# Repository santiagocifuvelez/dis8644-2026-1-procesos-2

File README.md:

# dis8644-2026-1-procesos-2

Este repositorio estuvo activo entre marzo y abril 2026, durante la segunda mitad del curso DIS8644 Taller de diseño de máquinas electrónicas.

Para el contexto global del curso, por favor visitar el repositorio <https://github.com/disenoUDP/dis8644-2026-1>

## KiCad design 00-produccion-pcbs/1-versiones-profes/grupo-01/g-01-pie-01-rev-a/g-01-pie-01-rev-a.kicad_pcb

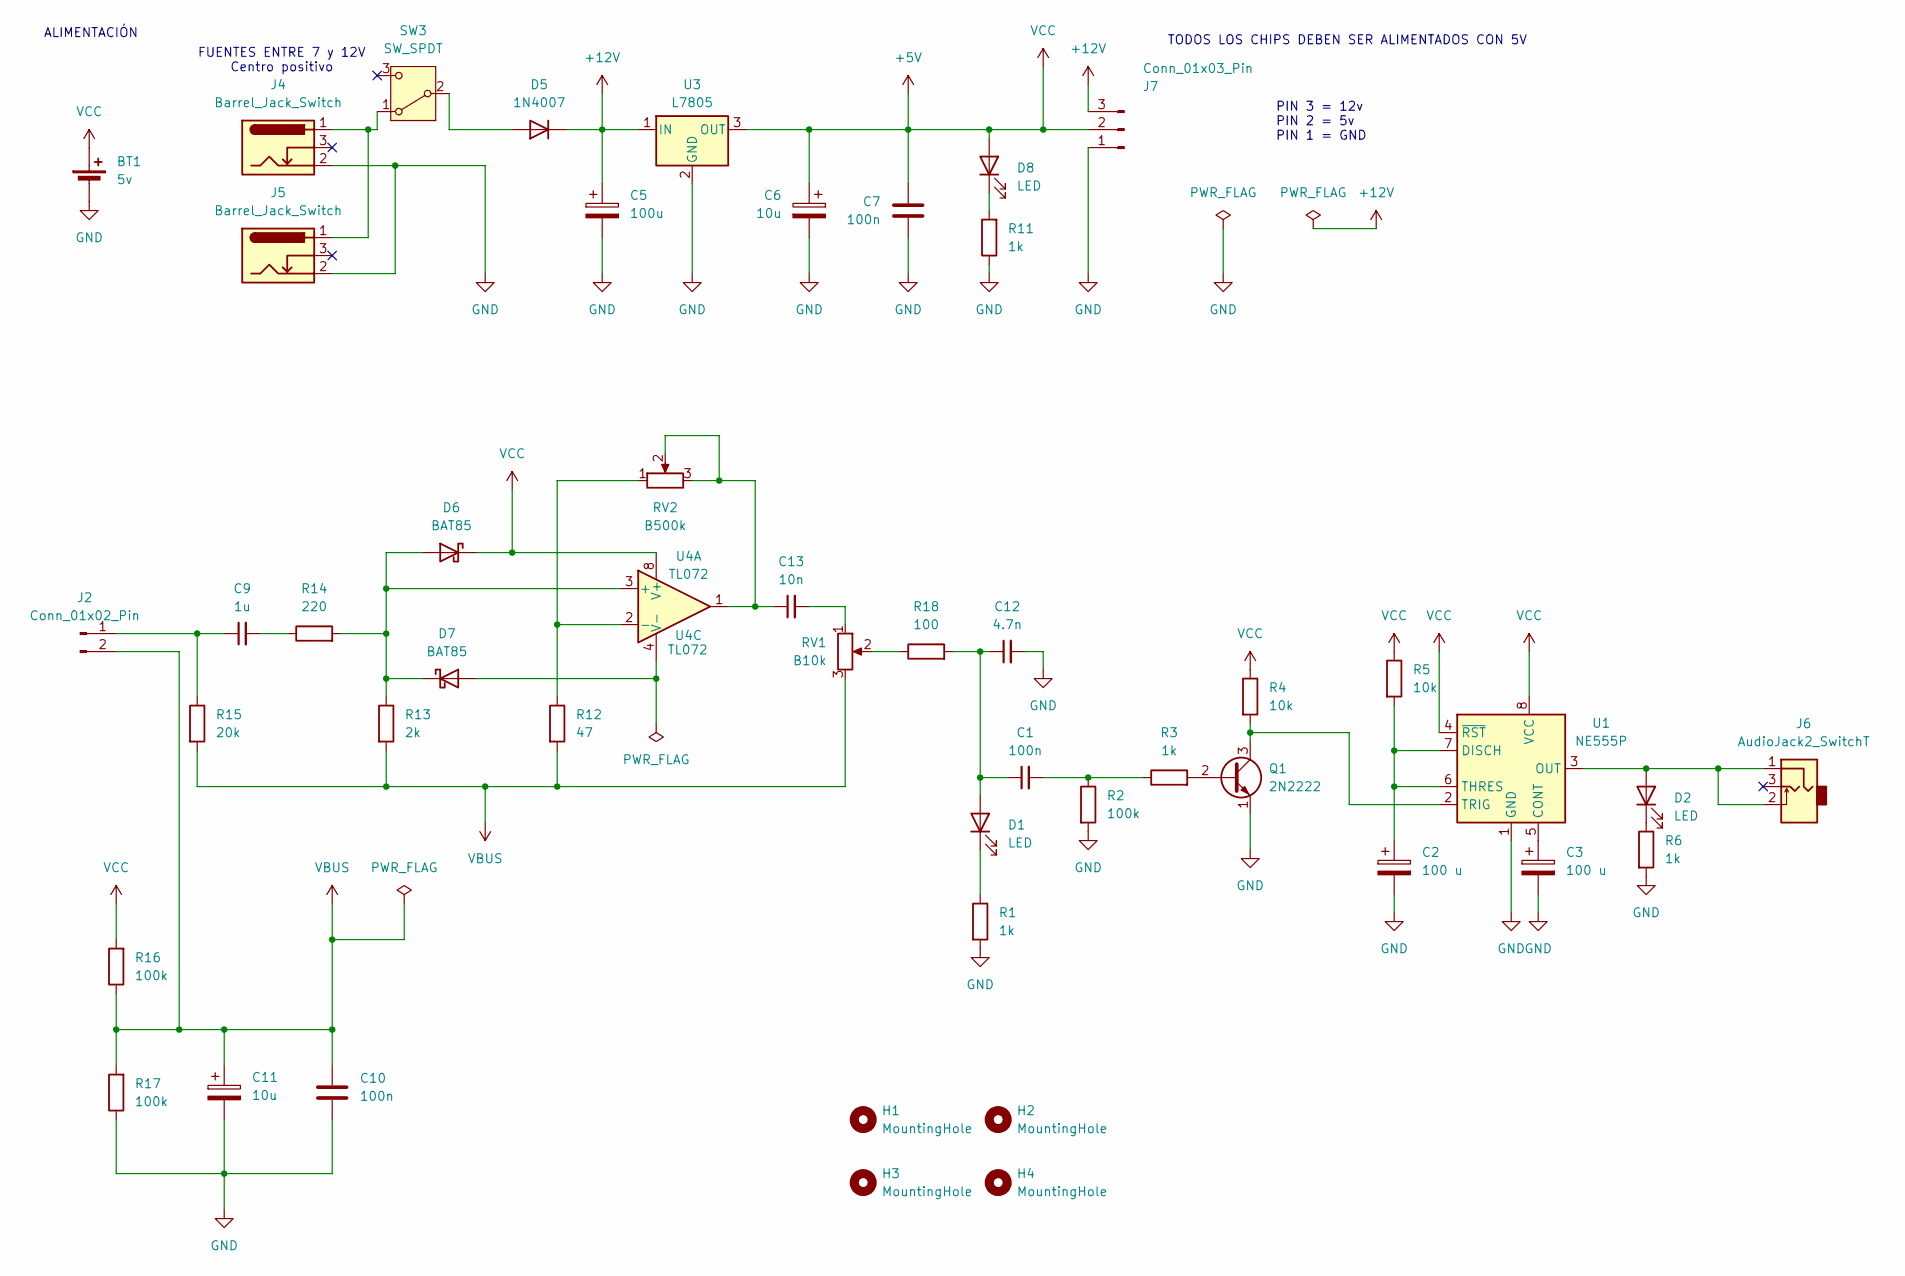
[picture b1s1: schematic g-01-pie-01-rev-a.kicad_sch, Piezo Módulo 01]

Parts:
BT1: 5v; TerminalBlock_MaiXu_MX126-5.0-02P_1x02_P5.00mm
C1, C7, C10: 100n; C_Disc_D5.0mm_W2.5mm_P2.50mm
C2, C3: 100 u; CP_Radial_D8.0mm_P3.80mm
C5: 100u; CP_Radial_D8.0mm_P3.80mm
C6, C11: 10u; CP_Radial_D4.0mm_P2.00mm
C9: 1u; C_Disc_D3.8mm_W2.6mm_P2.50mm
C12: 4.7n; C_Disc_D3.8mm_W2.6mm_P2.50mm
C13: 10n; C_Disc_D3.8mm_W2.6mm_P2.50mm
D1, D2, D8: LED; LED_D5.0mm
D5: 1N4007; D_DO-41_SOD81_P10.16mm_Horizontal
D6, D7: BAT85; D_DO-35_SOD27_P7.62mm_Horizontal
H1, H2, H3, H4: MountingHole; MountingHole_3.2mm_M3
J2: Conn_01x02_Pin; PinSocket_1x02_P2.54mm_Vertical
J4, J5: Barrel_Jack_Switch; BarrelJack_Horizontal
J6: AudioJack2_SwitchT; PJ301M-12
J7: Conn_01x03_Pin; PinSocket_1x03_P2.54mm_Vertical
Q1: 2N2222; TO-39-3
R1, R3, R6, R11: 1k; R_Axial_DIN0207_L6.3mm_D2.5mm_P10.16mm_Horizontal
R2, R16, R17: 100k; R_Axial_DIN0207_L6.3mm_D2.5mm_P10.16mm_Horizontal
R4, R5: 10k; R_Axial_DIN0207_L6.3mm_D2.5mm_P10.16mm_Horizontal
R12: 47; R_Axial_DIN0207_L6.3mm_D2.5mm_P10.16mm_Horizontal
R13: 2k; R_Axial_DIN0207_L6.3mm_D2.5mm_P10.16mm_Horizontal
R14: 220; R_Axial_DIN0207_L6.3mm_D2.5mm_P10.16mm_Horizontal
R15: 20k; R_Axial_DIN0207_L6.3mm_D2.5mm_P10.16mm_Horizontal
R18: 100; R_Axial_DIN0207_L6.3mm_D2.5mm_P10.16mm_Horizontal
RV1: B10k; Potentiometer_Alps_RK163_Single_Horizontal
RV2: B500k; Potentiometer_Alps_RK163_Single_Horizontal
SW3: SW_SPDT; spdt_ssd12d00g3
U1: NE555P; CERDIP-8_W7.62mm_SideBrazed_LongPads
U3: L7805; TO-220-3_Vertical
U4: TL072; CERDIP-8_W7.62mm_SideBrazed_LongPads

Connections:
+5V: BT1.1 (+), C6.1, C7.1, D6.1 (K), D8.2 (A), J7.2, R4.1, R5.1, R16.2, U1.4 (~RST), U1.8 (VCC), U3.3 (OUT), U4.8 (V+)
+12V: C5.1, D5.1 (K), J7.3, U3.1 (IN)
GND: BT1.2 (-), C2.2, C3.2, C5.2, C6.2, C7.2, C10.2, C11.2, C12.2, J4.2, J5.2, J7.1, Q1.1 (E), R1.2, R2.2, R6.2, R11.1, R17.1, U1.1 (GND), U3.2 (GND)
unnamed: C1.2, R2.1, R3.1
unnamed: C9.2, R14.1
unnamed: C13.1, RV2.2, RV2.3, U4.1
unnamed: C13.2, RV1.1
unnamed: C1.1, C12.1, D1.2 (A), R18.2
unnamed: D1.1 (K), R1.1
unnamed: D2.2 (A), J6.1, J6.2, U1.3 (OUT)
unnamed: D2.1 (K), R6.1
unnamed: D5.2 (A), SW3.2 (B)
unnamed: D6.2 (A), D7.1 (K), R13.1, R14.2, U4.3 (+)
unnamed: D7.2 (A), U4.4 (V-)
unnamed: D8.1 (K), R11.2
unnamed: C9.1, J2.1, R15.1
unnamed: Q1.2 (B), R3.2
unnamed: Q1.3 (C), R4.2, U1.2 (TRIG)
unnamed: R18.1, RV1.2
unnamed: J4.1, J5.1, SW3.1 (A)
unnamed: C3.1, U1.5 (CONT)
unnamed: C2.1, R5.2, U1.6 (THRES), U1.7 (DISCH)
unnamed: R12.1, RV2.1, U4.2 (-)
VBUS: C10.1, C11.1, J2.2, R12.2, R13.2, R15.2, R16.1, R17.2, RV1.3

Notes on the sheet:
TODOS LOS CHIPS DEBEN SER ALIMENTADOS CON 5V
PIN 3 = 12v PIN 2 = 5v PIN 1 = GND
FUENTES ENTRE 7 y 12V Centro positivo
ALIMENTACIÓN

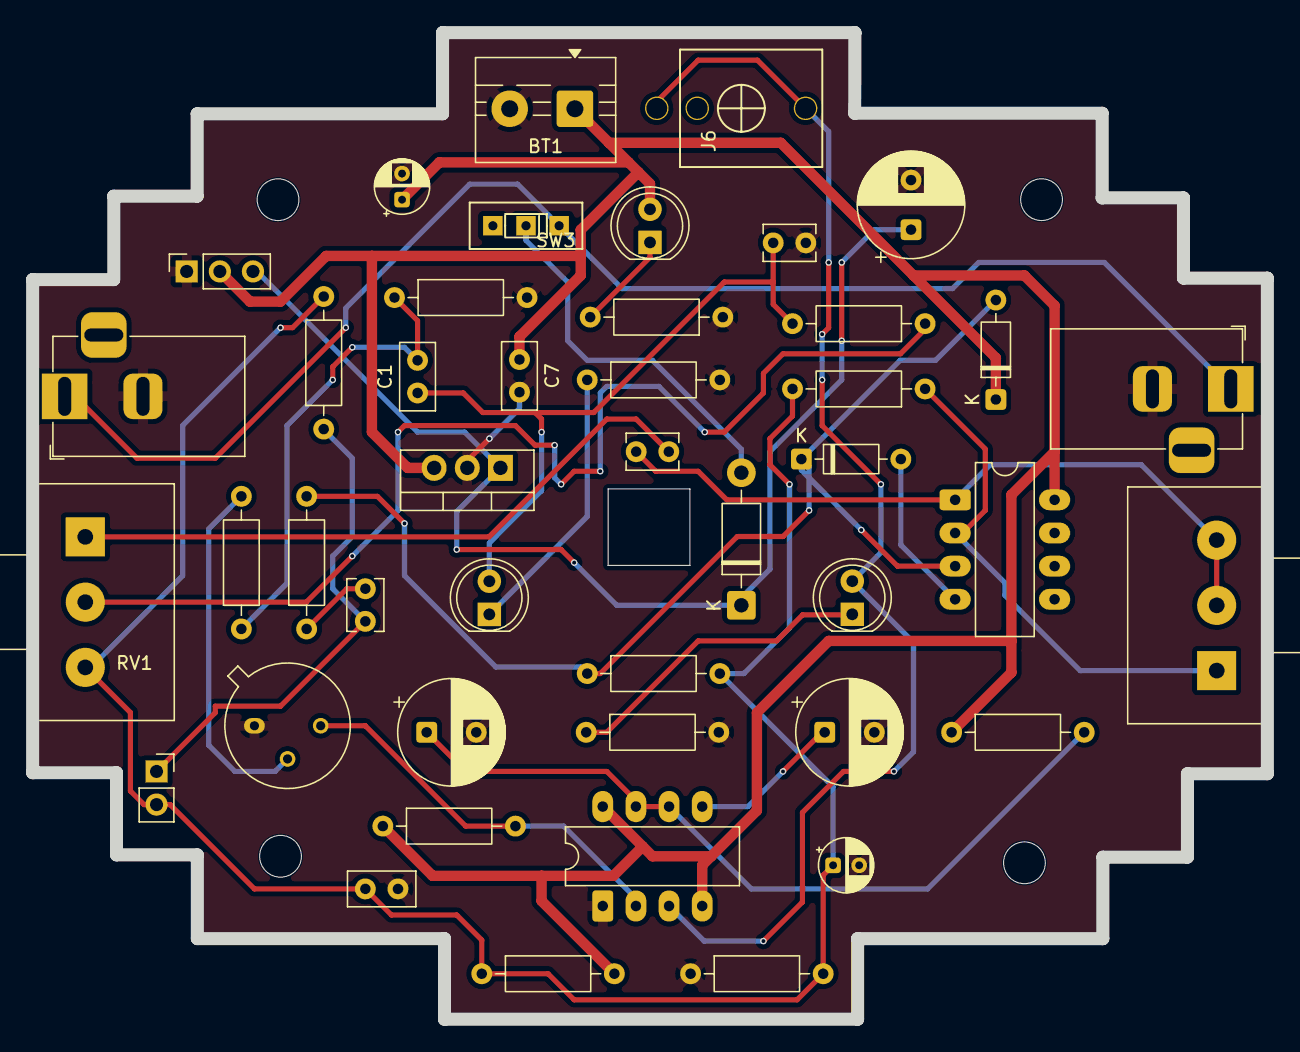
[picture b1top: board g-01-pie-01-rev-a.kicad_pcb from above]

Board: 2 copper layers, 94.6 x 75.6 mm, 48 parts (0 on the bottom side), 24 nets.

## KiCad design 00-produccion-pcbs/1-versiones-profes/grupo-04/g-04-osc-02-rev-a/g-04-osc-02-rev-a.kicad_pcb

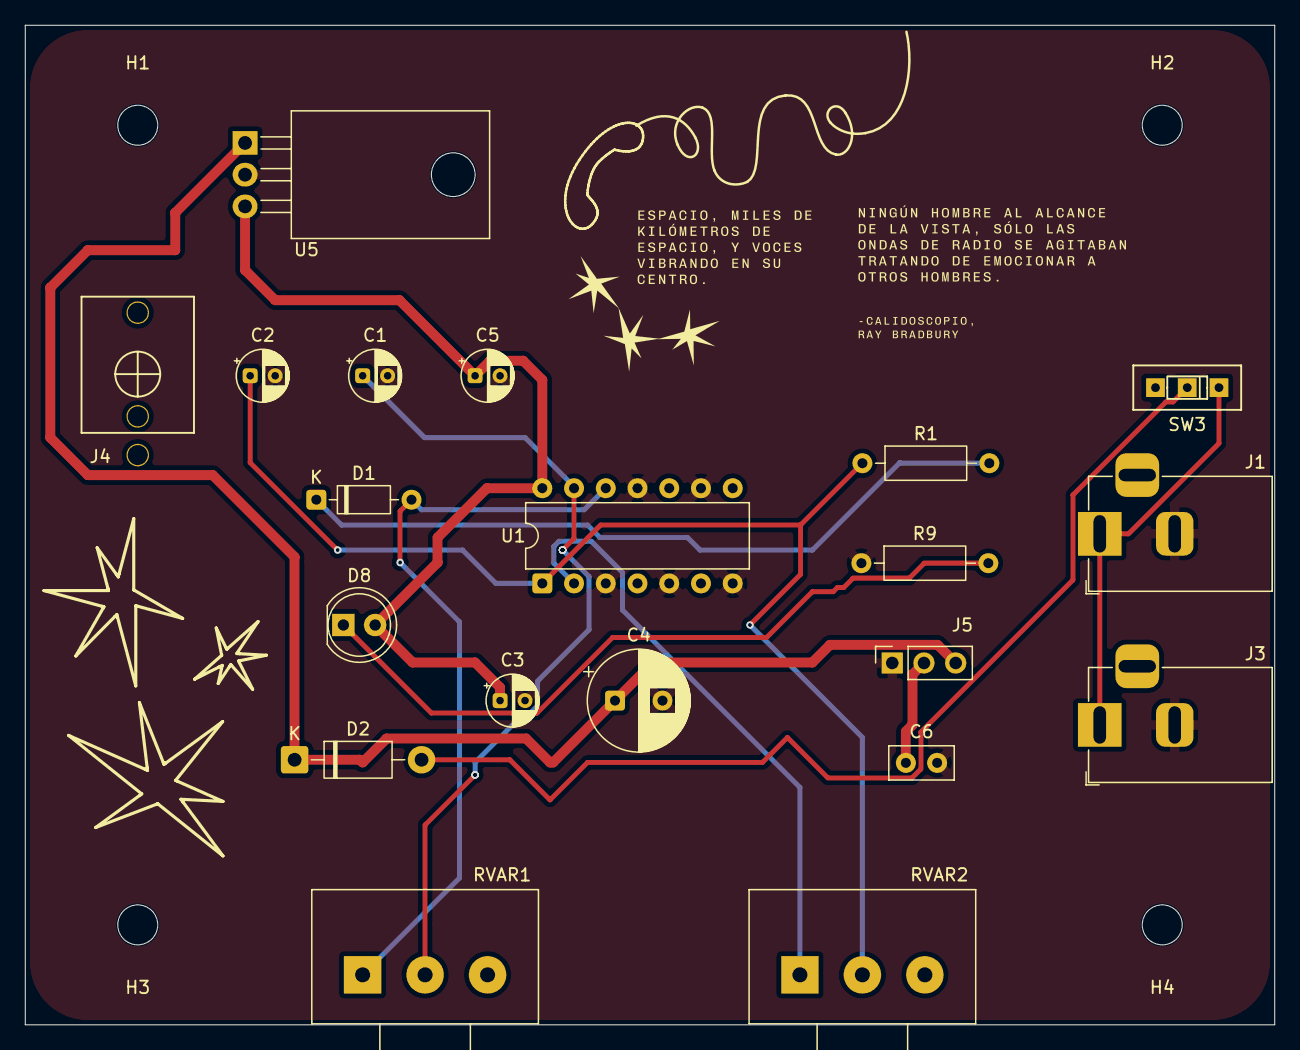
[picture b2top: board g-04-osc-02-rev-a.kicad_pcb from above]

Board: 2 copper layers, 100.0 x 80.0 mm, 24 parts (0 on the bottom side), 11 nets.

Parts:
C1, C2: 1u; CP_Radial_D4.0mm_P2.00mm
C3, C5: 10u; CP_Radial_D4.0mm_P2.00mm
C4: 100u; CP_Radial_D8.0mm_P3.80mm
C6: 100n; C_Disc_D5.0mm_W2.5mm_P2.50mm
D1: D_Small; D_DO-35_SOD27_P7.62mm_Horizontal
D2: 1N4007; D_DO-41_SOD81_P10.16mm_Horizontal
D8: LED; LED_D5.0mm
H1, H2, H3, H4: MountingHole; MountingHole_3.2mm_M3
J1, J3: Barrel_Jack_Switch; BarrelJack_Horizontal
J4: AudioJack2_SwitchT; PJ301M-12
J5: Conn_01x03_Pin; PinSocket_1x03_P2.54mm_Vertical
R1, R9: 1k; R_Axial_DIN0207_L6.3mm_D2.5mm_P10.16mm_Horizontal
RVAR1, RVAR2: 100K; Potentiometer_Alps_RK163_Single_Horizontal
SW3: SW_SPDT; spdt_ssd12d00g3
U1: 40106; DIP-14_W7.62mm
U5: L7805; TO-220-3_Horizontal_TabDown

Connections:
+5V: C3.1, C5.1, C6.1, D8.2 (A), J5.2, U1.14 (VDD), U5.3 (OUT)
+12V: C4.1, D2.1 (K), J5.3, U5.1 (IN)
GND: C1.2, C2.2, C3.2, C4.2, C5.2, C6.2, J1.2, J3.2, J5.1, R9.1, U1.3, U1.5, U1.7 (VSS), U1.9, U1.11, U5.2 (GND)
unnamed: C1.1, RVAR1.2, U1.13
unnamed: C2.1, R1.1, RVAR2.2, U1.1
unnamed: D1.2 (A), RVAR1.1, U1.12
unnamed: D1.1 (K), R1.2
unnamed: D2.2 (A), SW3.2 (B)
unnamed: D8.1 (K), R9.2
unnamed: J1.1, J3.1, SW3.1 (A)
Output: RVAR2.1, U1.2

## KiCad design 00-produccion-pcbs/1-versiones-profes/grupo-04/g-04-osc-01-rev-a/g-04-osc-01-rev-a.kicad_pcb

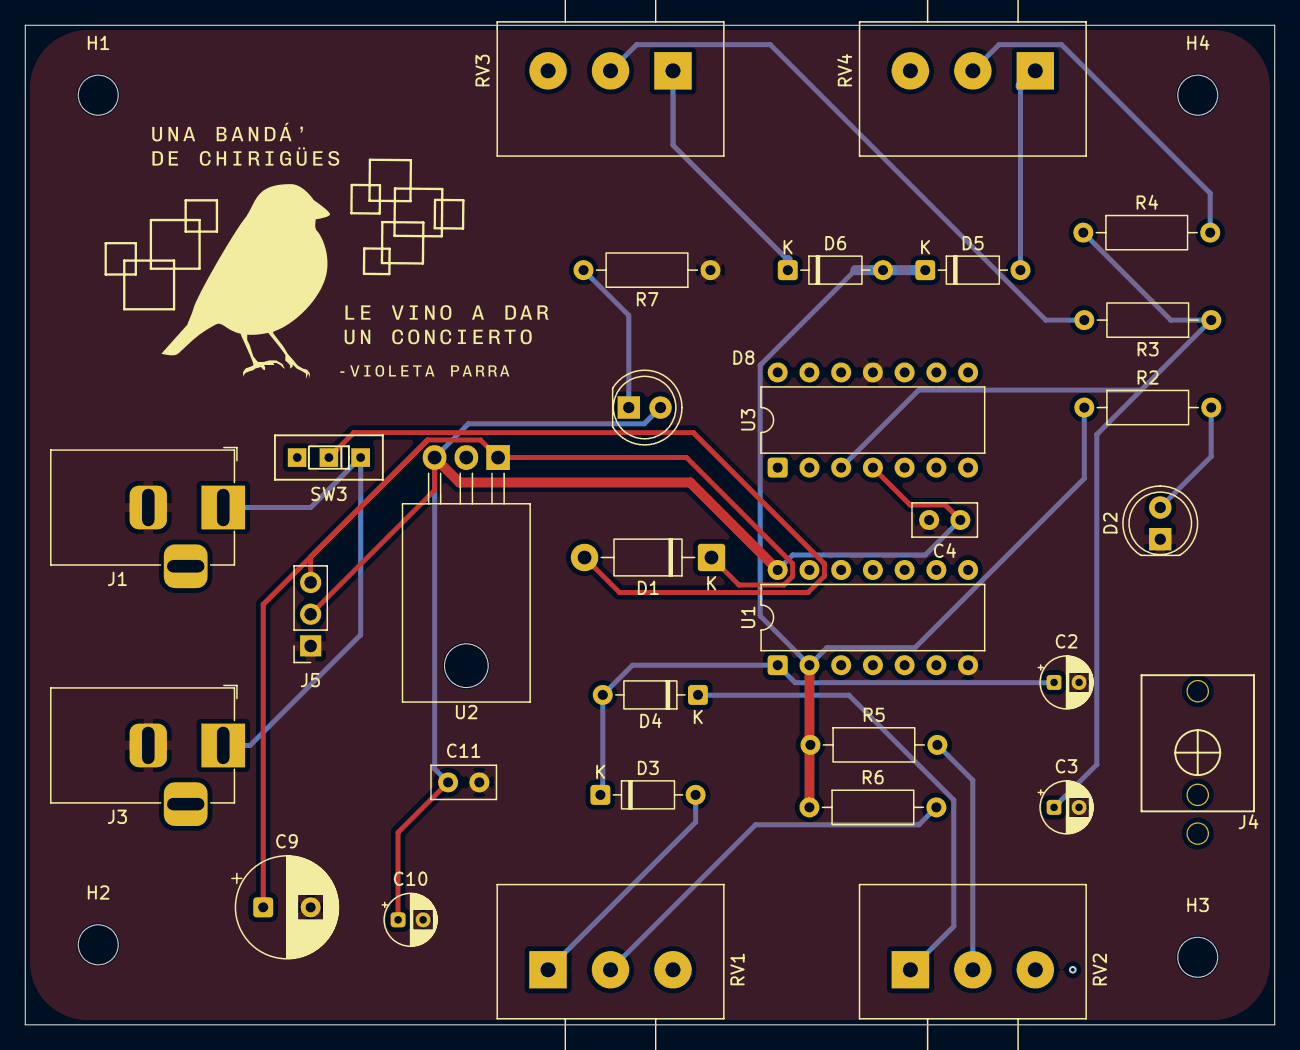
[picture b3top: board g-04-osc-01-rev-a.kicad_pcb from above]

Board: 2 copper layers, 100.0 x 80.0 mm, 35 parts (0 on the bottom side), 19 nets.

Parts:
C2, C3, C10: 10u; CP_Radial_D4.0mm_P2.00mm
C4, C11: 100n; C_Disc_D5.0mm_W2.5mm_P2.50mm
C9: 100u; CP_Radial_D8.0mm_P3.80mm
D1: 1N4007; D_DO-41_SOD81_P10.16mm_Horizontal
D2, D8: LED; LED_D5.0mm
D3, D4, D5, D6: 1N4148; D_DO-35_SOD27_P7.62mm_Horizontal
H1, H2, H3, H4: MountingHole; MountingHole_3.2mm_M3
J1, J3: Barrel_Jack_Switch; BarrelJack_Horizontal
J4: AudioJack2_SwitchT; PJ301M-12
J5: Conn_01x03_Pin; PinSocket_1x03_P2.54mm_Vertical
R2, R3, R4, R5, R6: 1K; R_Axial_DIN0207_L6.3mm_D2.5mm_P10.16mm_Horizontal
R7: 1k; R_Axial_DIN0207_L6.3mm_D2.5mm_P10.16mm_Horizontal
RV1, RV2, RV3, RV4: 100K; Potentiometer_Alps_RK163_Single_Horizontal
SW3: SW_SPDT; spdt_ssd12d00g3
U1: 40106; DIP-14_W7.62mm
U2: L7805; TO-220-3_Horizontal_TabDown
U3: LM324; DIP-14_W7.62mm

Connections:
+5V: C4.1, C10.1, C11.1, D8.2 (A), J5.2, U1.14 (VDD), U2.3 (OUT), U3.4 (V+)
+12V: C9.1, D1.1 (K), J5.3, U2.1 (IN)
GND: C2.2, C3.2, C4.2, C9.2, C10.2, C11.2, D2.1 (K), J1.2, J3.2, J5.1, R7.1, U1.7 (VSS), U2.2 (GND), U3.11 (V-)
unnamed: D1.2 (A), SW3.2 (B)
unnamed: D2.2 (A), R2.2
unnamed: D3.2 (A), RV1.1
unnamed: C2.1, D3.1 (K), D4.2 (A), U1.1
unnamed: D4.1 (K), RV2.1
unnamed: D5.2 (A), RV4.1
unnamed: D5.1 (K), D6.2 (A), R2.1, R5.1, R6.1, U1.2
unnamed: D6.1 (K), RV3.1
unnamed: D8.1 (K), R7.2
unnamed: R3.2, RV3.2
unnamed: R4.2, RV4.2
unnamed: R5.2, RV2.2
unnamed: R6.2, RV1.2
unnamed: J1.1, J3.1, SW3.1 (A)
unnamed: C3.1, R3.1, R4.1, U3.3 (+)
OUTPUT: U3.1, U3.2 (-)

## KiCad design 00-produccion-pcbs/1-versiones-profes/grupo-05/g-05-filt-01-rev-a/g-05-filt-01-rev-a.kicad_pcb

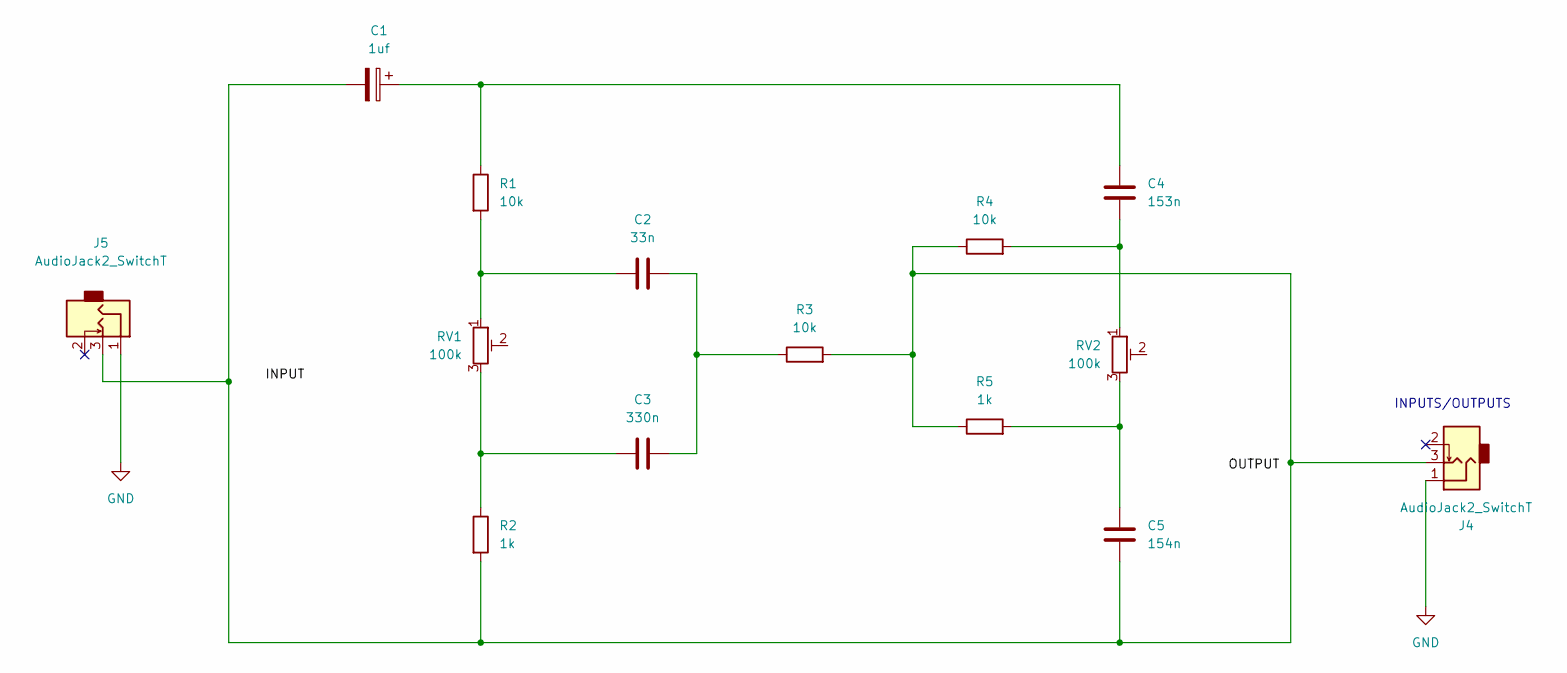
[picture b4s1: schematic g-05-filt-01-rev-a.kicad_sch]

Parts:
C1: 1uf; CP_Radial_D5.0mm_P2.00mm
C2: 33n; C_Disc_D10.5mm_W5.0mm_P7.50mm
C3: 330n; C_Disc_D7.5mm_W5.0mm_P10.00mm
C4: 153n; C_Disc_D6.0mm_W2.5mm_P5.00mm
C5: 154n; C_Disc_D7.5mm_W4.4mm_P5.00mm
J4, J5: AudioJack2_SwitchT; PJ301M-12
R1, R3, R4: 10k; R_Axial_DIN0207_L6.3mm_D2.5mm_P2.54mm_Vertical
R2, R5: 1k; R_Axial_DIN0207_L6.3mm_D2.5mm_P2.54mm_Vertical
RV1, RV2: 100k; Potentiometer_Bourns_PTV09A-1_Single_Vertical

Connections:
GND: J4.1, J5.1
unnamed: C1.1, C4.1, R1.1
unnamed: C1.2, C5.2, J4.3, J5.3, R2.2, R3.2, R4.1, R5.1
unnamed: C2.1, R1.2, RV1.1
unnamed: C2.2, C3.2, R3.1
unnamed: C3.1, R2.1, RV1.3
unnamed: C4.2, R4.2, RV2.1
unnamed: C5.1, R5.2, RV2.3

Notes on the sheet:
INPUTS/OUTPUTS

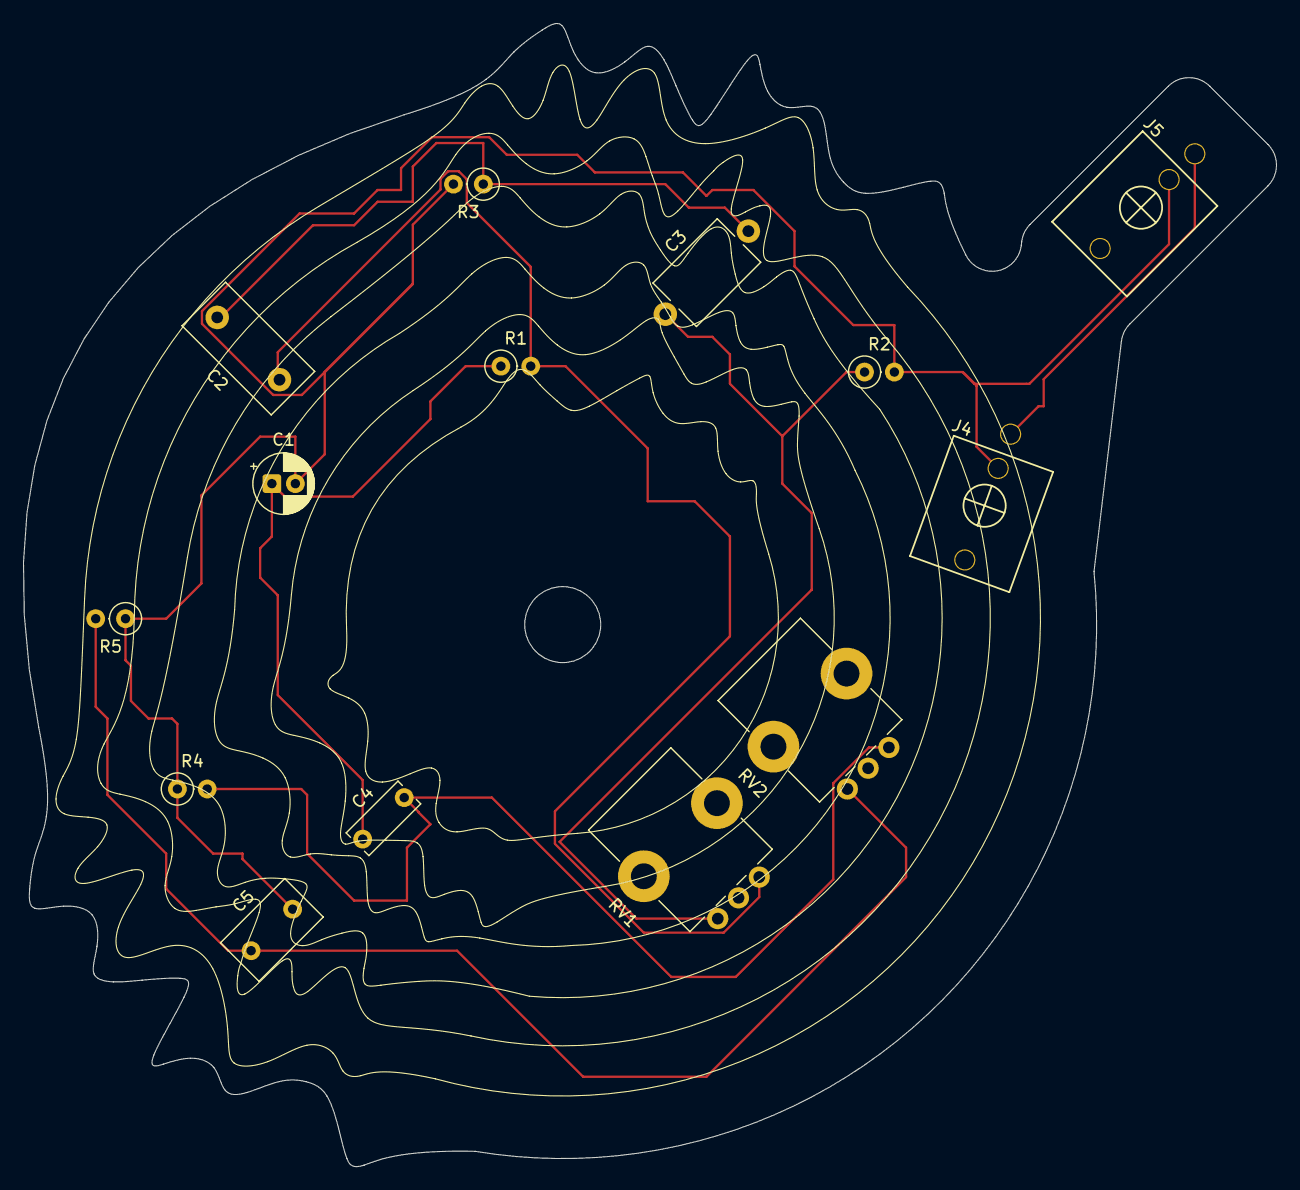
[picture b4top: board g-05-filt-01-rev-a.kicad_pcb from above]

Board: 2 copper layers, 106.7 x 97.3 mm, 14 parts (0 on the bottom side), 8 nets.

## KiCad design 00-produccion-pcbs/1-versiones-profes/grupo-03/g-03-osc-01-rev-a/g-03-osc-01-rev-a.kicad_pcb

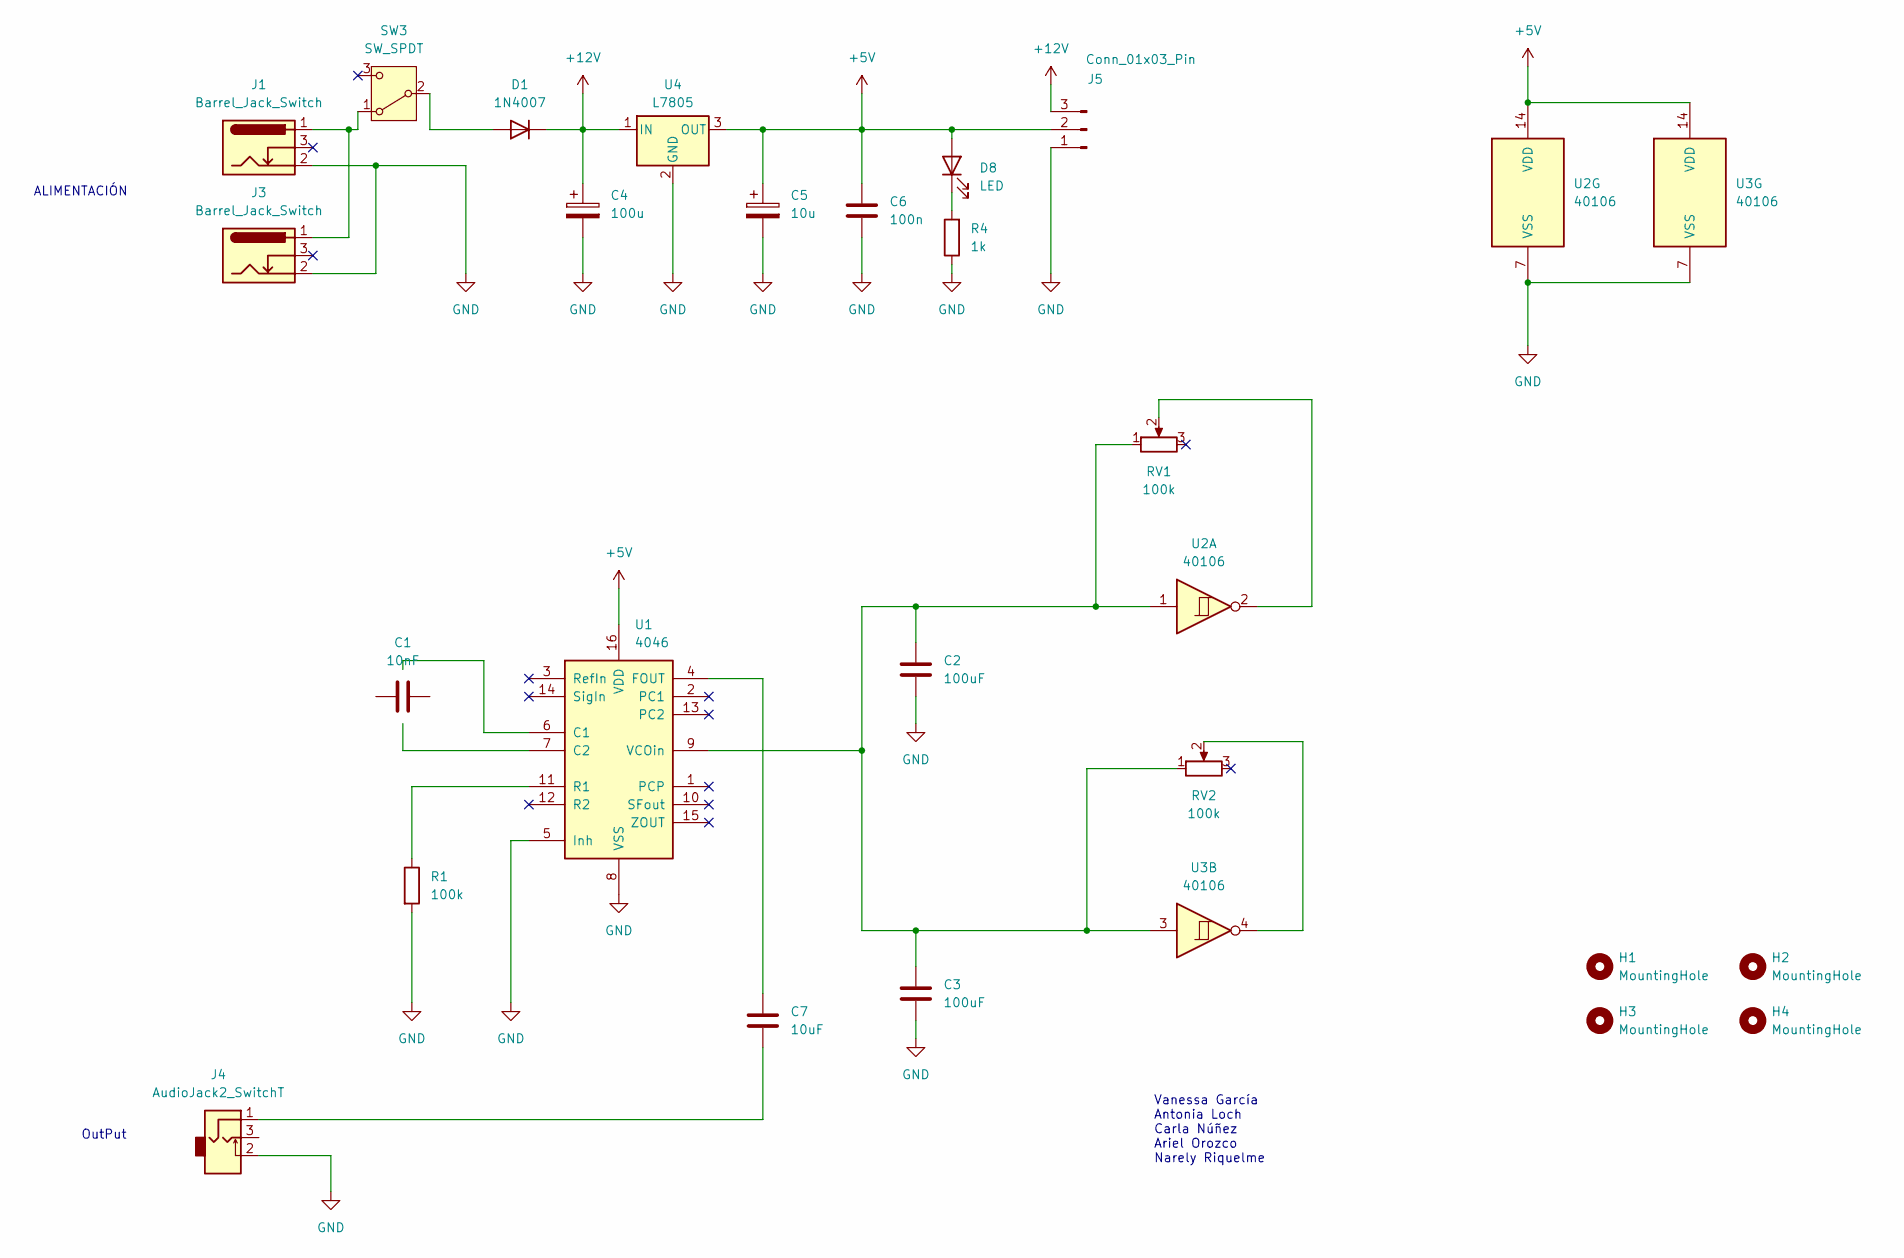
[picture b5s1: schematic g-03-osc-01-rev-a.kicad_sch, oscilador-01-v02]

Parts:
C1: 10nF; C_Disc_D3.8mm_W2.6mm_P2.50mm
C2, C3: 100uF; CP_Radial_D6.3mm_P2.50mm
C4: 100u; CP_Radial_D8.0mm_P3.80mm
C5: 10u; CP_Radial_D4.0mm_P2.00mm
C6: 100n; C_Disc_D5.0mm_W2.5mm_P2.50mm
C7: 10uF; CP_Radial_D5.0mm_P2.00mm
D1: 1N4007; D_DO-41_SOD81_P10.16mm_Horizontal
D8: LED; LED_D5.0mm
H1, H2, H3, H4: MountingHole; MountingHole_3.2mm_M3
J1, J3: Barrel_Jack_Switch; BarrelJack_Horizontal
J4: AudioJack2_SwitchT; PJ301M-12
J5: Conn_01x03_Pin; PinSocket_1x03_P2.54mm_Vertical
R1: 100k; R_Axial_DIN0207_L6.3mm_D2.5mm_P10.16mm_Horizontal
R4: 1k; R_Axial_DIN0207_L6.3mm_D2.5mm_P10.16mm_Horizontal
RV1, RV2: 100k; Potentiometer_Alps_RK163_Single_Horizontal
SW3: SW_SPDT; spdt_ssd12d00g3
U1: 4046; DIP-16_W7.62mm_LongPads
U2, U3: 40106; DIP-14_W7.62mm_LongPads
U4: L7805; TO-220-3_Horizontal_TabDown

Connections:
+5V: C5.1, C6.1, D8.2 (A), J5.2, U1.16 (VDD), U2.14 (VDD), U3.14 (VDD), U4.3 (OUT)
+12V: C4.1, D1.1 (K), J5.3, U4.1 (IN)
GND: C2.2, C3.2, C4.2, C5.2, C6.2, J1.2, J3.2, J4.2, J5.1, R1.2, R4.1, U1.5 (Inh), U1.8 (VSS), U2.7 (VSS), U3.7 (VSS), U4.2 (GND)
unnamed: C7.2, J4.1
unnamed: D1.2 (A), SW3.2 (B)
unnamed: D8.1 (K), R4.2
unnamed: RV1.2, U2.2
unnamed: RV2.2, U3.4
unnamed: J1.1, J3.1, SW3.1 (A)
unnamed: C7.1, U1.4 (FOUT)
unnamed: R1.1, U1.11 (R1)
unnamed: C2.1, C3.1, RV1.1, RV2.1, U1.9 (VCOin), U2.1, U3.3

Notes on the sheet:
ALIMENTACIÓN
OutPut
Vanessa García Antonia Loch Carla Núñez Ariel Orozco Narely Riquelme

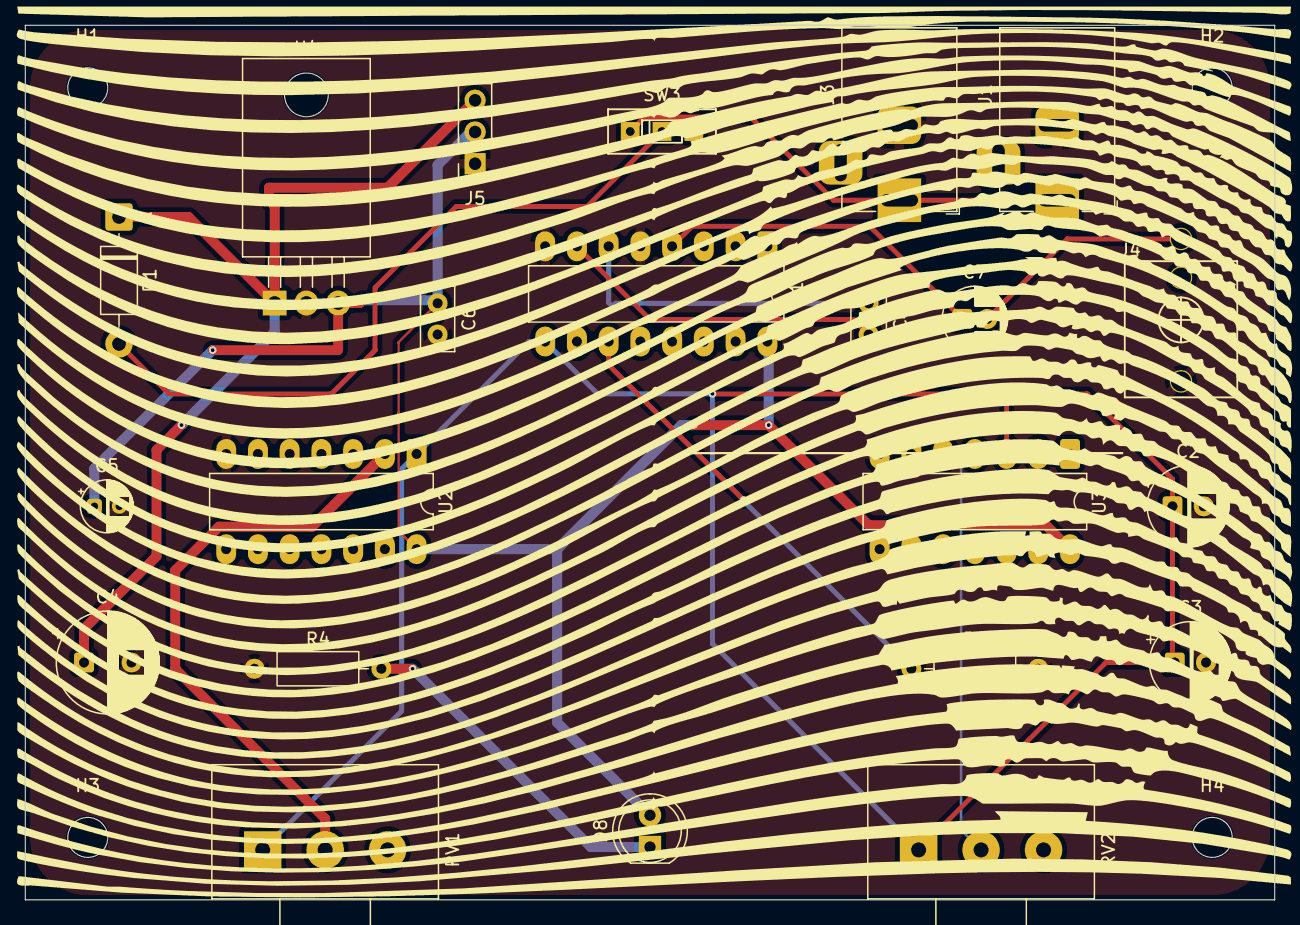
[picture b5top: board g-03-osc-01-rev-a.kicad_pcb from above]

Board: 2 copper layers, 100.0 x 70.0 mm, 26 parts (0 on the bottom side), 12 nets.

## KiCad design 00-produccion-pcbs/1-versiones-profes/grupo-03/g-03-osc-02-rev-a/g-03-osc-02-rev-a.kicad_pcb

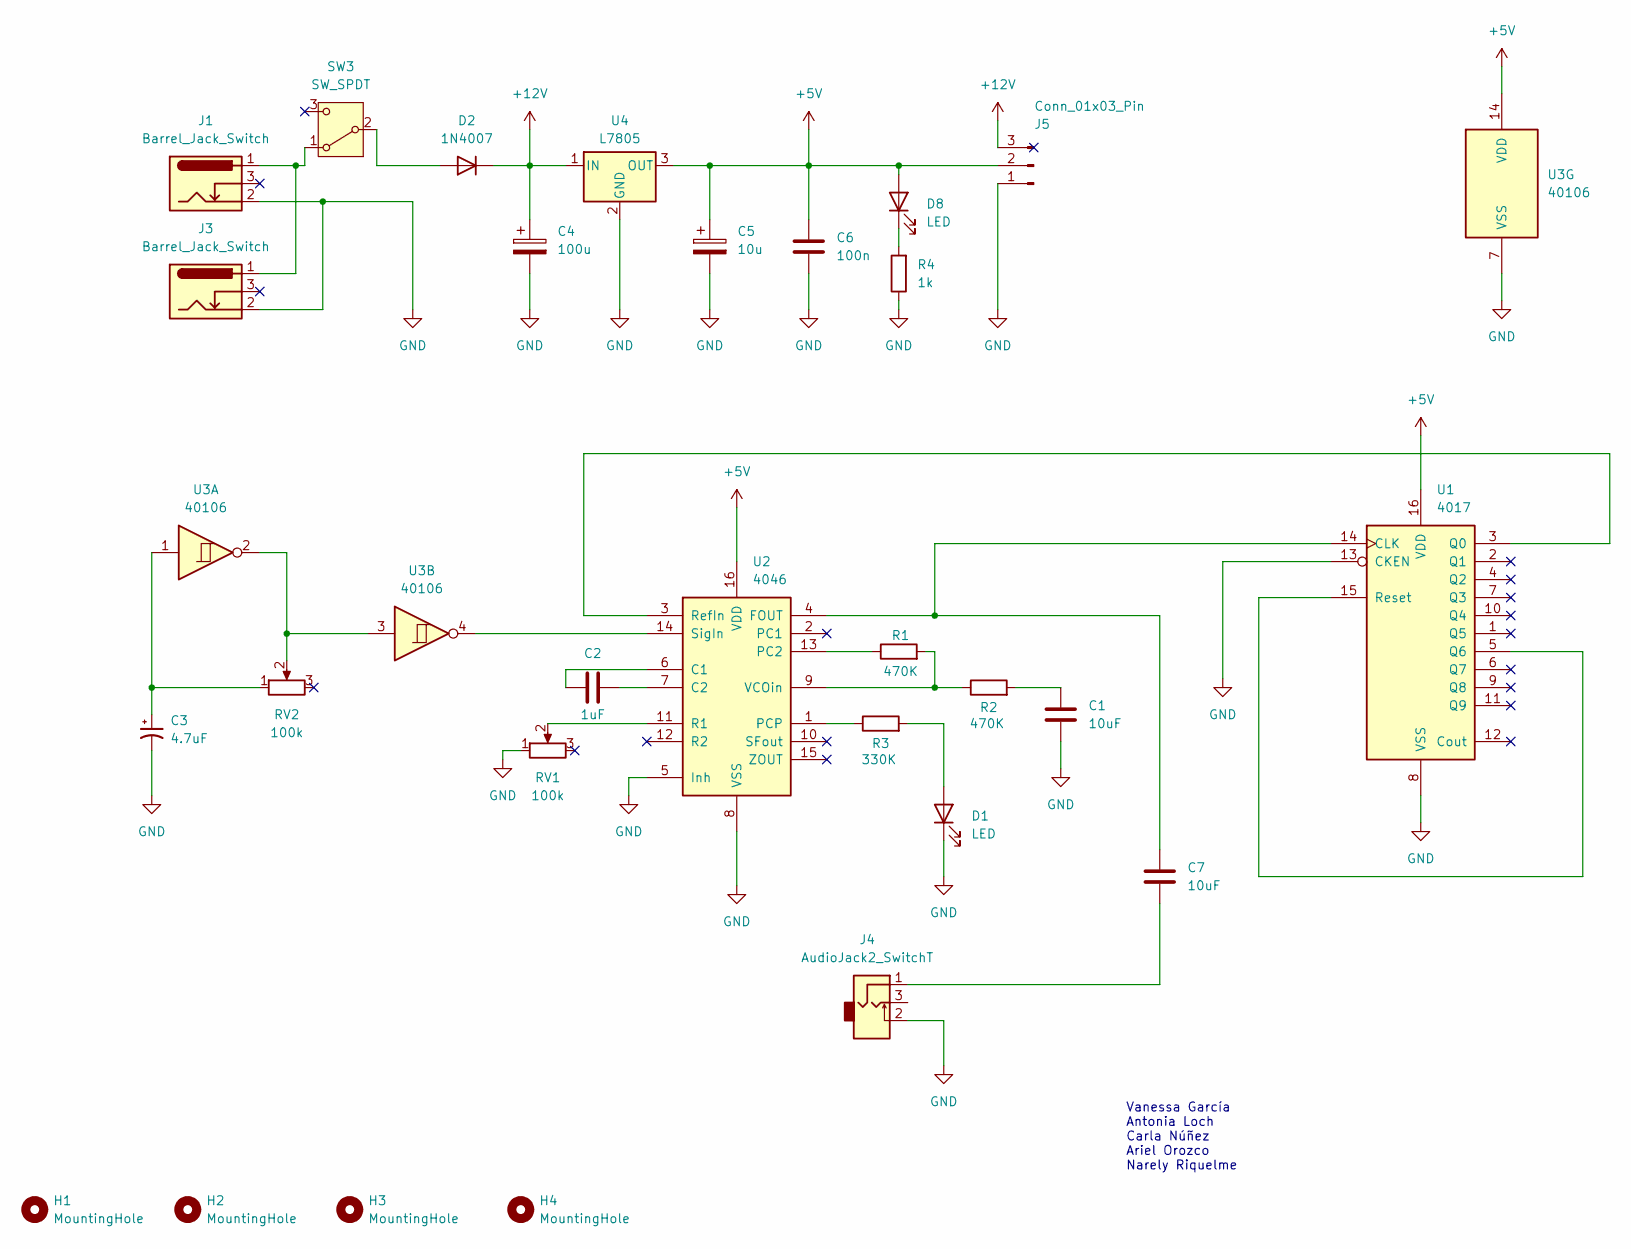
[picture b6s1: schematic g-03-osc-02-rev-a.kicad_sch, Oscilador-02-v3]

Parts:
C1, C7: 10uF; CP_Radial_D5.0mm_P2.00mm
C2: 1uF; CP_Radial_D5.0mm_P2.00mm
C3: 4.7uF; CP_Radial_D5.0mm_P2.00mm
C4: 100u; CP_Radial_D8.0mm_P3.80mm
C5: 10u; CP_Radial_D4.0mm_P2.00mm
C6: 100n; C_Disc_D5.0mm_W2.5mm_P2.50mm
D1, D8: LED; LED_D5.0mm
D2: 1N4007; D_DO-41_SOD81_P10.16mm_Horizontal
H1, H2, H3, H4: MountingHole; MountingHole_3.2mm_M3
J1, J3: Barrel_Jack_Switch; BarrelJack_Horizontal
J4: AudioJack2_SwitchT; PJ301M-12
J5: Conn_01x03_Pin; PinSocket_1x03_P2.54mm_Vertical
R1, R2: 470K; R_Axial_DIN0207_L6.3mm_D2.5mm_P10.16mm_Horizontal
R3: 330K; R_Axial_DIN0207_L6.3mm_D2.5mm_P10.16mm_Horizontal
R4: 1k; R_Axial_DIN0207_L6.3mm_D2.5mm_P10.16mm_Horizontal
RV1, RV2: 100k; Potentiometer_Alps_RK163_Single_Horizontal
SW3: SW_SPDT; spdt_ssd12d00g3
U1: 4017; DIP-16_W7.62mm_LongPads
U2: 4046; DIP-16_W7.62mm_LongPads
U3: 40106; DIP-14_W7.62mm_LongPads
U4: L7805; TO-220-3_Horizontal_TabDown

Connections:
+5V: C5.1, C6.1, D8.2 (A), J5.2, U1.16 (VDD), U2.16 (VDD), U3.14 (VDD), U4.3 (OUT)
+12V: C4.1, D2.1 (K), J5.3, U4.1 (IN)
GND: C1.2, C3.2, C4.2, C5.2, C6.2, D1.1 (K), J1.2, J3.2, J4.2, J5.1, R4.1, RV1.1, U1.8 (VSS), U1.13 (CKEN), U2.5 (Inh), U2.8 (VSS), U3.7 (VSS), U4.2 (GND)
unnamed: C1.1, R2.2
unnamed: C3.1, RV2.1, U3.1
unnamed: C7.2, J4.1
unnamed: D1.2 (A), R3.2
unnamed: D2.2 (A), SW3.2 (B)
unnamed: D8.1 (K), R4.2
unnamed: RV2.2, U3.2, U3.3
unnamed: J1.1, J3.1, SW3.1 (A)
unnamed: C7.1, U1.14 (CLK), U2.4 (FOUT)
unnamed: U1.3 (Q0), U2.3 (RefIn)
unnamed: U1.5 (Q6), U1.15 (Reset)
unnamed: C2.1, U2.6 (C1)
unnamed: C2.2, U2.7 (C2)
unnamed: R1.1, U2.13 (PC2)
unnamed: R3.1, U2.1 (PCP)
unnamed: RV1.2, U2.11 (R1)
unnamed: U2.14 (SigIn), U3.4
unnamed: R1.2, R2.1, U2.9 (VCOin)

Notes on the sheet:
Vanessa García Antonia Loch Carla Núñez Ariel Orozco Narely Riquelme

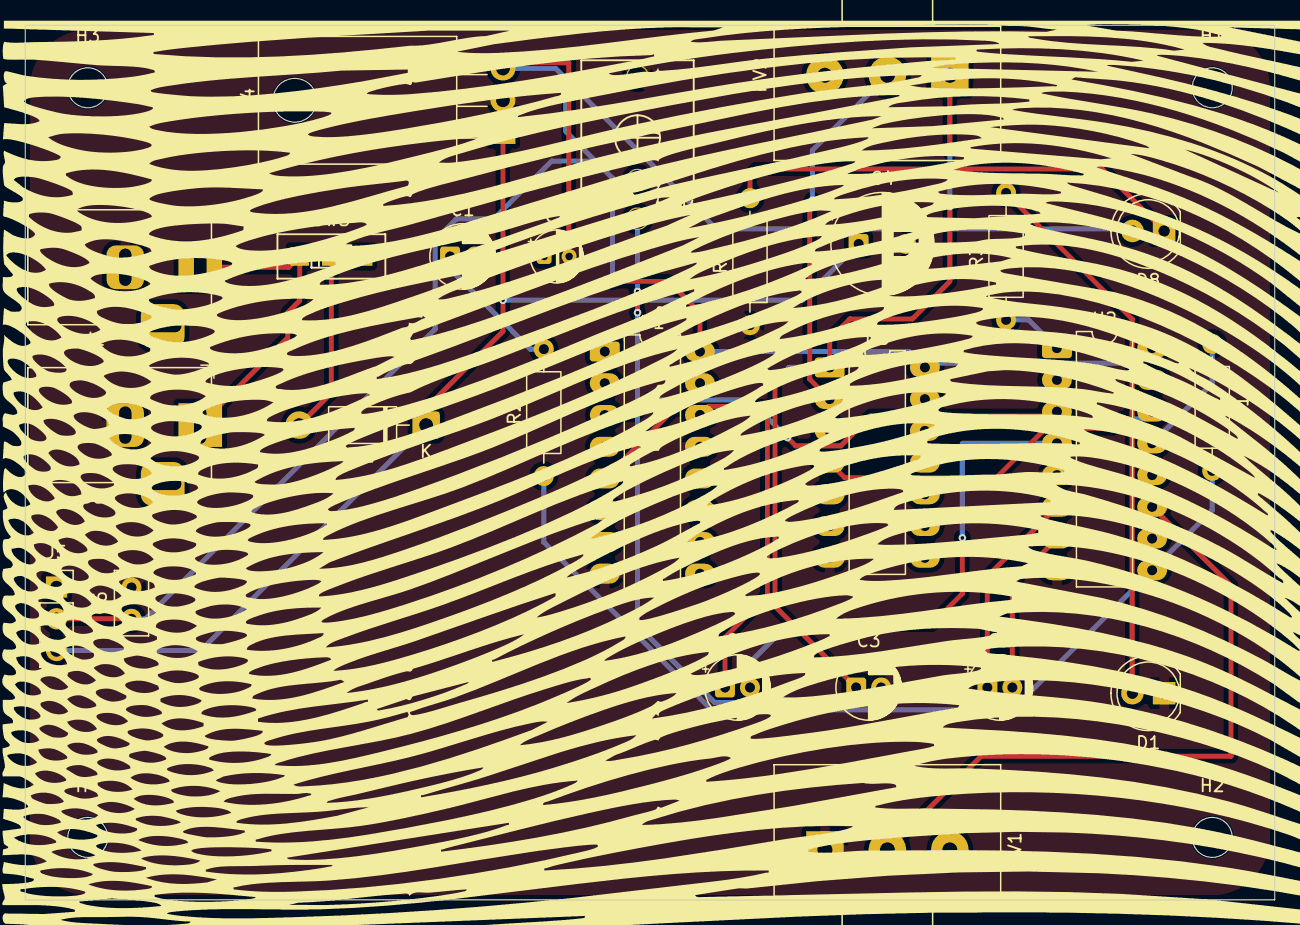
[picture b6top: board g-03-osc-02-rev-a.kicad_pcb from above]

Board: 2 copper layers, 100.0 x 70.0 mm, 29 parts (0 on the bottom side), 21 nets.
